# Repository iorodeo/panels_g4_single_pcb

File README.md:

## panels_g4_single_pcb

Prototype designs for a single PCB G4 panels variant.

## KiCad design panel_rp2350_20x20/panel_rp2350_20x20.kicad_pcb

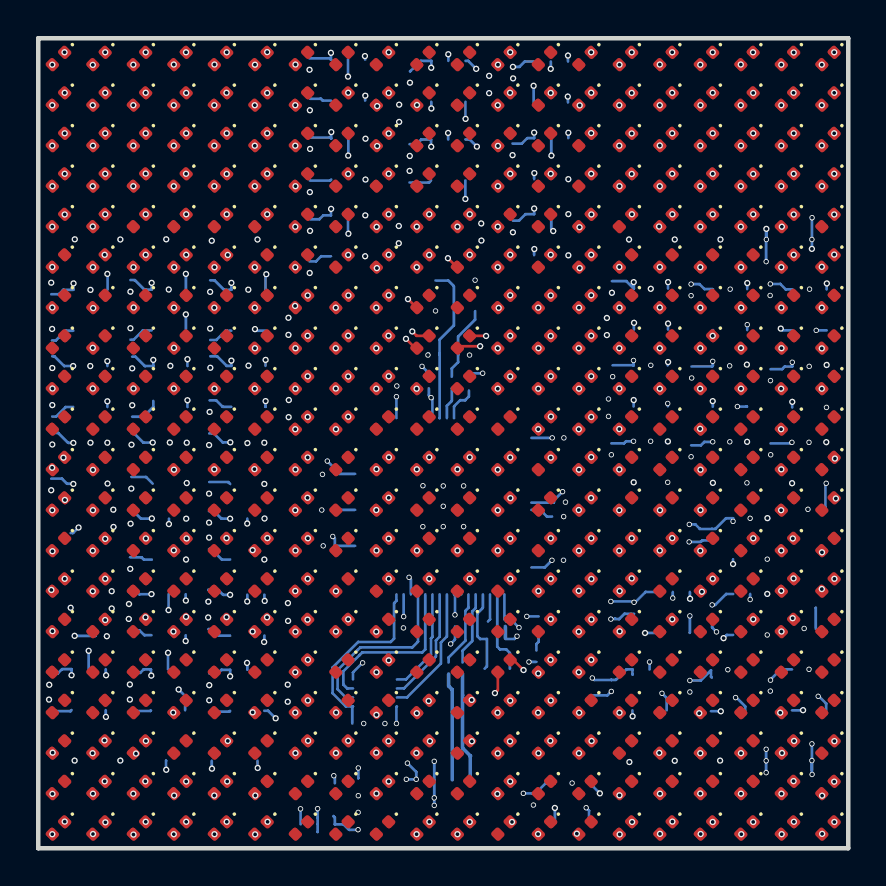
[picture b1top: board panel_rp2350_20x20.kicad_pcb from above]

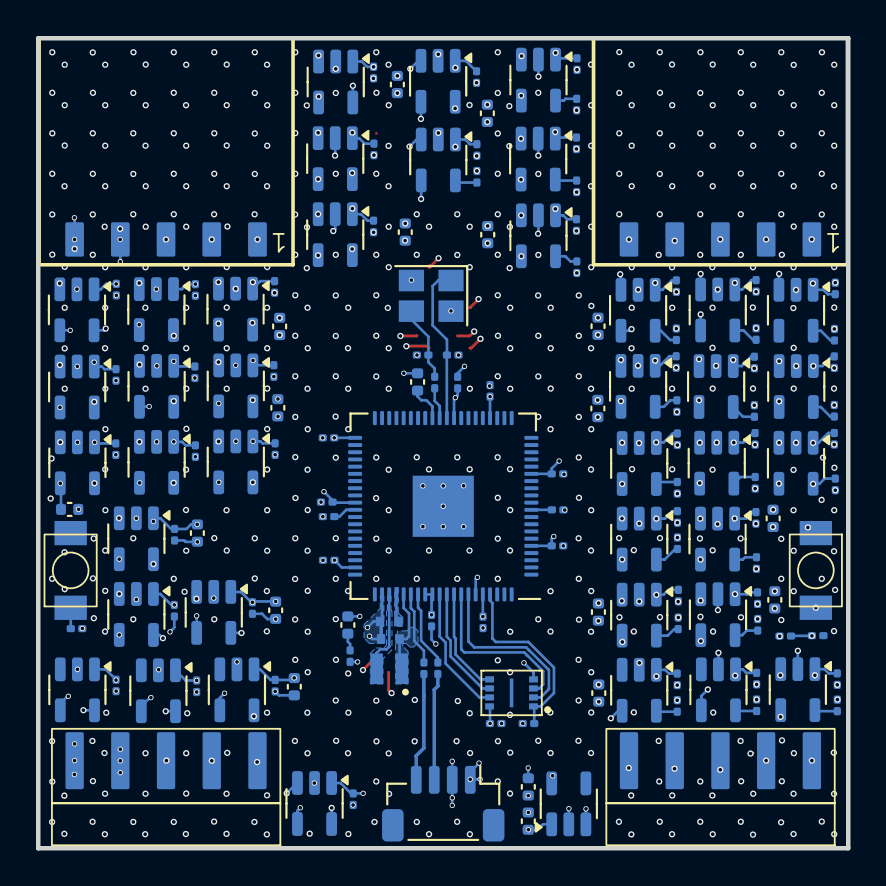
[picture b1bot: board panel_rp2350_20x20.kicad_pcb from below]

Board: 6 copper layers, 45.0 x 45.0 mm, 556 parts (156 on the bottom side), 131 nets.

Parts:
C1, C2: 15pF; C_0201_0603Metric
C3, C6, C9, C10, C11, C12, C13, C14, C15, C16, C17, C18, C19, C20, C21, C22, C23, C24, C25, C26, C27, C28, C29, C30, C31, C32, C33, C34, C35, C36, C37, C38, C39, C40, C41, C42, C43, C44, C45, C46, C47, C48, C49, C50, C51, C52, C53, C54, C55, C56, C57, C58: 100nF; C_0201_0603Metric
C4, C5: 4.7uF; C_0402_1005Metric_small_pads
C7, C8: 4.7uF; C_0402_1005Metric
C59, C60, C61, C62, C63, C64, C65, C66, C67, C68, C69, C70, C71, C72, C73, C74, C75, C76: 10uF; C_0402_1005Metric
D1: LED_T0; LED_0402_1005Metric
D2, D3, D4, D5, D6, D7, D8, D9, D10, D11, D12, D13, D14, D15, D16, D17, D18, D19, D20, D21, D22, D23, D24, D25, D26, D27, D28, D29, D30, D31, D32, D33, D34, D35, D36, D37, D38, D39, D40, D41, D42, D43, D44, D45, D46, D47, D48, D49, D50, D51, D52, D53, D54, D55, D56, D57, D58, D59, D60, D61, D62, D63, D64, D65, D66, D67, D68, D69, D70, D71, D72, D73, D74, D75, D76, D77, D78, D79, D80, D81, D82, D83, D84, D85, D86, D87, D88, D89, D90, D91, D92, D93, D94, D95, D96, D97, D98, D99, D100, D101, D102, D103, D104, D105, D106, D107, D108, D109, D110, D111, D112, D113, D114, D115, D116, D117, D118, D119, D120, D121, D122, D123, D124, D125, D126, D127, D128, D129, D130, D131, D132, D133, D134, D135, D136, D137, D138, D139, D140, D141, D142, D143, D144, D145, D146, D147, D148, D149, D150, D151, D152, D153, D154, D155, D156, D157, D158, D159, D160, D161, D162, D163, D164, D165, D166, D167, D168, D169, D170, D171, D172, D173, D174, D175, D176, D177, D178, D179, D180, D181, D182, D183, D184, D185, D186, D187, D188, D189, D190, D191, D192, D193, D194, D195, D196, D197, D198, D199, D200, D201, D202, D203, D204, D205, D206, D207, D208, D209, D210, D211, D212, D213, D214, D215, D216, D217, D218, D219, D220, D221, D222, D223, D224, D225, D226, D227, D228, D229, D230, D231, D232, D233, D234, D235, D236, D237, D238, D239, D240, D241, D242, D243, D244, D245, D246, D247, D248, D249, D250, D251, D252, D253, D254, D255, D256, D257, D258, D259, D260, D261, D262, D263, D264, D265, D266, D267, D268, D269, D270, D271, D272, D273, D274, D275, D276, D277, D278, D279, D280, D281, D282, D283, D284, D285, D286, D287, D288, D289, D290, D291, D292, D293, D294, D295, D296, D297, D298, D299, D300, D301, D302, D303, D304, D305, D306, D307, D308, D309, D310, D311, D312, D313, D314, D315, D316, D317, D318, D319, D320, D321, D322, D323, D324, D325, D326, D327, D328, D329, D330, D331, D332, D333, D334, D335, D336, D337, D338, D339, D340, D341, D342, D343, D344, D345, D346, D347, D348, D349, D350, D351, D352, D353, D354, D355, D356, D357, D358, D359, D360, D361, D362, D363, D364, D365, D366, D367, D368, D369, D370, D371, D372, D373, D374, D375, D376, D377, D378, D379, D380, D381, D382, D383, D384, D385, D386, D387, D388, D389, D390, D391, D392, D393, D394, D395, D396, D397, D398, D399, D400: LED; LED_0402_1005Metric
J1: Conn_01x04; JST_SH_BM04B-SRSS-TB_1x04-1MP_P1.00mm_Vertical
J2, J3: Conn_01x05; PinHeader_1x5_M20-8890545R
J4, J5: Conn_01x05; ConnRcpt_1x5_SMH-105-02-X-S
L1: 3.3uH; L_pol_2016
R1, R4: 10k; R_0201_0603Metric
R2, R3, R5: 1k; R_0201_0603Metric
R6: 33; R_0201_0603Metric
R7, R8: 27; R_0201_0603Metric
R9, R10, R11, R12, R13, R14, R15, R16, R17, R18, R19, R20, R21, R22, R23, R24, R25, R26, R27, R28: 270; R_0201_0603Metric
SW1, SW2: SW_Push; TS-1088-AR02016
U1: APS6404L-3SQR; flashmem_PSON50P300X200X60-9N
U2: RP2354B_80QFN; RP2350-QFN-80-1EP_10x10_P0.4mm_EP3.4x3.4mm_ThermalVias
U3, U4, U5, U6, U7, U8, U9, U10, U11, U12, U13, U14, U15, U16, U17, U18, U19, U20, U21, U22, U23, U24, U25, U26, U27, U28, U29, U30, U31, U32, U33, U34, U35, U36, U37, U38, U39, U40, U41, U42: UCC27517; SOT-23-5
U43: AP2112K-3.3; SOT-23-5
Y1: ABM8-272-T3; Crystal_SMD_3225-4Pin_3.2x2.5mm

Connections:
+1V1: C5.1, C6.1, C8.1, C9.1, L1.1, U2.10 (DVDD), U2.32 (DVDD), U2.51 (DVDD), U2.65 (VREG_FB)
+3V3: C3.1, C4.1, C10.1, C11.1, C12.1, C13.1, C14.1, C15.1, C16.1, C17.1, C18.1, C68.1, R1.1, R4.1, R6.1, U1.8 (VCC), U2.5 (IOVDD), U2.15 (IOVDD), U2.24 (IOVDD), U2.29 (IOVDD), U2.41 (IOVDD), U2.50 (IOVDD), U2.59 (ADC_AVDD), U2.60 (IOVDD), U2.64 (VREG_VIN), U2.68 (USB_OTP_VDD), U2.69 (QSPI_IOVDD), U2.76 (IOVDD), U43.5 (VOUT)
+5V: C19.1, C20.1, C21.1, C22.1, C23.1, C24.1, C25.1, C26.1, C27.1, C28.1, C29.1, C30.1, C31.1, C32.1, C33.1, C34.1, C35.1, C36.1, C37.1, C38.1, C39.1, C40.1, C41.1, C42.1, C43.1, C44.1, C45.1, C46.1, C47.1, C48.1, C49.1, C50.1, C51.1, C52.1, C53.1, C54.1, C55.1, C56.1, C57.1, C58.1, C59.1, C60.1, C61.1, C62.1, C63.1, C64.1, C65.1, C66.1, C67.1, C69.1, C70.1, C71.1, C72.1, C73.1, C74.1, C75.1, C76.1, J1.2, J2.5, J4.5, U3.1 (VDD), U4.1 (VDD), U5.1 (VDD), U6.1 (VDD), U7.1 (VDD), U8.1 (VDD), U9.1 (VDD), U10.1 (VDD), U11.1 (VDD), U12.1 (VDD), U13.1 (VDD), U14.1 (VDD), U15.1 (VDD), U16.1 (VDD), U17.1 (VDD), U18.1 (VDD), U19.1 (VDD), U20.1 (VDD), U21.1 (VDD), U22.1 (VDD), U23.1 (VDD), U24.1 (VDD), U25.1 (VDD), U26.1 (VDD), U27.1 (VDD), U28.1 (VDD), U29.1 (VDD), U30.1 (VDD), U31.1 (VDD), U32.1 (VDD), U33.1 (VDD), U34.1 (VDD), U35.1 (VDD), U36.1 (VDD), U37.1 (VDD), U38.1 (VDD), U39.1 (VDD), U40.1 (VDD), U41.1 (VDD), U42.1 (VDD), U43.1 (VIN), U43.3 (EN)
/drivers/COL_00: R9.1, U3.5 (OUT)
/drivers/COL_01: R10.1, U4.5 (OUT)
/drivers/COL_02: R11.1, U5.5 (OUT)
/drivers/COL_03: R12.1, U6.5 (OUT)
/drivers/COL_04: R13.1, U7.5 (OUT)
/drivers/COL_05: R14.1, U8.5 (OUT)
/drivers/COL_06: R15.1, U9.5 (OUT)
/drivers/COL_07: R16.1, U10.5 (OUT)
/drivers/COL_08: R17.1, U11.5 (OUT)
/drivers/COL_09: R18.1, U12.5 (OUT)
/drivers/COL_10: R19.1, U13.5 (OUT)
/drivers/COL_11: R20.1, U14.5 (OUT)
/drivers/COL_12: R21.1, U15.5 (OUT)
/drivers/COL_13: R22.1, U16.5 (OUT)
/drivers/COL_14: R23.1, U17.5 (OUT)
/drivers/COL_15: R24.1, U18.5 (OUT)
/drivers/COL_16: R25.1, U19.5 (OUT)
/drivers/COL_17: R26.1, U20.5 (OUT)
/drivers/COL_18: R27.1, U21.5 (OUT)
/drivers/COL_19: R28.1, U22.5 (OUT)
/drivers/COL_MCU_00: U2.78 (GPIO1), U3.3 (IN+)
/drivers/COL_MCU_01: U2.79 (GPIO2), U4.3 (IN+)
/drivers/COL_MCU_02: U2.80 (GPIO3), U5.3 (IN+)
/drivers/COL_MCU_03: U2.1 (GPIO4), U6.3 (IN+)
/drivers/COL_MCU_04: U2.2 (GPIO5), U7.3 (IN+)
/drivers/COL_MCU_05: U2.3 (GPIO6), U8.3 (IN+)
/drivers/COL_MCU_06: U2.4 (GPIO7), U9.3 (IN+)
/drivers/COL_MCU_07: U2.6 (GPIO8), U10.3 (IN+)
/drivers/COL_MCU_08: U2.7 (GPIO9), U11.3 (IN+)
/drivers/COL_MCU_09: U2.8 (GPIO10), U12.3 (IN+)
/drivers/COL_MCU_10: U2.9 (GPIO11), U13.3 (IN+)
/drivers/COL_MCU_11: U2.11 (GPIO12), U14.3 (IN+)
/drivers/COL_MCU_12: U2.12 (GPIO13), U15.3 (IN+)
/drivers/COL_MCU_13: U2.13 (GPIO14), U16.3 (IN+)
/drivers/COL_MCU_14: U2.14 (GPIO15), U17.3 (IN+)
/drivers/COL_MCU_15: U2.16 (GPIO16), U18.3 (IN+)
/drivers/COL_MCU_16: U2.17 (GPIO17), U19.3 (IN+)
/drivers/COL_MCU_17: U2.18 (GPIO18), U20.3 (IN+)
/drivers/COL_MCU_18: U2.19 (GPIO19), U21.3 (IN+)
/drivers/COL_MCU_19: U2.20 (GPIO20), U22.3 (IN+)
/drivers/ROW_00: D1.1 (K), D21.1 (K), D41.1 (K), D61.1 (K), D81.1 (K), D101.1 (K), D121.1 (K), D141.1 (K), D161.1 (K), D181.1 (K), D201.1 (K), D221.1 (K), D241.1 (K), D261.1 (K), D281.1 (K), D301.1 (K), D321.1 (K), D341.1 (K), D361.1 (K), D381.1 (K), U23.5 (OUT)
/drivers/ROW_01: D2.1 (K), D22.1 (K), D42.1 (K), D62.1 (K), D82.1 (K), D102.1 (K), D122.1 (K), D142.1 (K), D162.1 (K), D182.1 (K), D202.1 (K), D222.1 (K), D242.1 (K), D262.1 (K), D282.1 (K), D302.1 (K), D322.1 (K), D342.1 (K), D362.1 (K), D382.1 (K), U24.5 (OUT)
/drivers/ROW_02: D3.1 (K), D23.1 (K), D43.1 (K), D63.1 (K), D83.1 (K), D103.1 (K), D123.1 (K), D143.1 (K), D163.1 (K), D183.1 (K), D203.1 (K), D223.1 (K), D243.1 (K), D263.1 (K), D283.1 (K), D303.1 (K), D323.1 (K), D343.1 (K), D363.1 (K), D383.1 (K), U25.5 (OUT)
/drivers/ROW_03: D4.1 (K), D24.1 (K), D44.1 (K), D64.1 (K), D84.1 (K), D104.1 (K), D124.1 (K), D144.1 (K), D164.1 (K), D184.1 (K), D204.1 (K), D224.1 (K), D244.1 (K), D264.1 (K), D284.1 (K), D304.1 (K), D324.1 (K), D344.1 (K), D364.1 (K), D384.1 (K), U26.5 (OUT)
/drivers/ROW_04: D5.1 (K), D25.1 (K), D45.1 (K), D65.1 (K), D85.1 (K), D105.1 (K), D125.1 (K), D145.1 (K), D165.1 (K), D185.1 (K), D205.1 (K), D225.1 (K), D245.1 (K), D265.1 (K), D285.1 (K), D305.1 (K), D325.1 (K), D345.1 (K), D365.1 (K), D385.1 (K), U27.5 (OUT)
/drivers/ROW_05: D6.1 (K), D26.1 (K), D46.1 (K), D66.1 (K), D86.1 (K), D106.1 (K), D126.1 (K), D146.1 (K), D166.1 (K), D186.1 (K), D206.1 (K), D226.1 (K), D246.1 (K), D266.1 (K), D286.1 (K), D306.1 (K), D326.1 (K), D346.1 (K), D366.1 (K), D386.1 (K), U28.5 (OUT)
/drivers/ROW_06: D7.1 (K), D27.1 (K), D47.1 (K), D67.1 (K), D87.1 (K), D107.1 (K), D127.1 (K), D147.1 (K), D167.1 (K), D187.1 (K), D207.1 (K), D227.1 (K), D247.1 (K), D267.1 (K), D287.1 (K), D307.1 (K), D327.1 (K), D347.1 (K), D367.1 (K), D387.1 (K), U29.5 (OUT)
/drivers/ROW_07: D8.1 (K), D28.1 (K), D48.1 (K), D68.1 (K), D88.1 (K), D108.1 (K), D128.1 (K), D148.1 (K), D168.1 (K), D188.1 (K), D208.1 (K), D228.1 (K), D248.1 (K), D268.1 (K), D288.1 (K), D308.1 (K), D328.1 (K), D348.1 (K), D368.1 (K), D388.1 (K), U30.5 (OUT)
/drivers/ROW_08: D9.1 (K), D29.1 (K), D49.1 (K), D69.1 (K), D89.1 (K), D109.1 (K), D129.1 (K), D149.1 (K), D169.1 (K), D189.1 (K), D209.1 (K), D229.1 (K), D249.1 (K), D269.1 (K), D289.1 (K), D309.1 (K), D329.1 (K), D349.1 (K), D369.1 (K), D389.1 (K), U31.5 (OUT)
/drivers/ROW_09: D10.1 (K), D30.1 (K), D50.1 (K), D70.1 (K), D90.1 (K), D110.1 (K), D130.1 (K), D150.1 (K), D170.1 (K), D190.1 (K), D210.1 (K), D230.1 (K), D250.1 (K), D270.1 (K), D290.1 (K), D310.1 (K), D330.1 (K), D350.1 (K), D370.1 (K), D390.1 (K), U32.5 (OUT)
/drivers/ROW_10: D11.1 (K), D31.1 (K), D51.1 (K), D71.1 (K), D91.1 (K), D111.1 (K), D131.1 (K), D151.1 (K), D171.1 (K), D191.1 (K), D211.1 (K), D231.1 (K), D251.1 (K), D271.1 (K), D291.1 (K), D311.1 (K), D331.1 (K), D351.1 (K), D371.1 (K), D391.1 (K), U33.5 (OUT)
/drivers/ROW_11: D12.1 (K), D32.1 (K), D52.1 (K), D72.1 (K), D92.1 (K), D112.1 (K), D132.1 (K), D152.1 (K), D172.1 (K), D192.1 (K), D212.1 (K), D232.1 (K), D252.1 (K), D272.1 (K), D292.1 (K), D312.1 (K), D332.1 (K), D352.1 (K), D372.1 (K), D392.1 (K), U34.5 (OUT)
/drivers/ROW_12: D13.1 (K), D33.1 (K), D53.1 (K), D73.1 (K), D93.1 (K), D113.1 (K), D133.1 (K), D153.1 (K), D173.1 (K), D193.1 (K), D213.1 (K), D233.1 (K), D253.1 (K), D273.1 (K), D293.1 (K), D313.1 (K), D333.1 (K), D353.1 (K), D373.1 (K), D393.1 (K), U35.5 (OUT)
/drivers/ROW_13: D14.1 (K), D34.1 (K), D54.1 (K), D74.1 (K), D94.1 (K), D114.1 (K), D134.1 (K), D154.1 (K), D174.1 (K), D194.1 (K), D214.1 (K), D234.1 (K), D254.1 (K), D274.1 (K), D294.1 (K), D314.1 (K), D334.1 (K), D354.1 (K), D374.1 (K), D394.1 (K), U36.5 (OUT)
/drivers/ROW_14: D15.1 (K), D35.1 (K), D55.1 (K), D75.1 (K), D95.1 (K), D115.1 (K), D135.1 (K), D155.1 (K), D175.1 (K), D195.1 (K), D215.1 (K), D235.1 (K), D255.1 (K), D275.1 (K), D295.1 (K), D315.1 (K), D335.1 (K), D355.1 (K), D375.1 (K), D395.1 (K), U37.5 (OUT)
/drivers/ROW_15: D16.1 (K), D36.1 (K), D56.1 (K), D76.1 (K), D96.1 (K), D116.1 (K), D136.1 (K), D156.1 (K), D176.1 (K), D196.1 (K), D216.1 (K), D236.1 (K), D256.1 (K), D276.1 (K), D296.1 (K), D316.1 (K), D336.1 (K), D356.1 (K), D376.1 (K), D396.1 (K), U38.5 (OUT)
/drivers/ROW_16: D17.1 (K), D37.1 (K), D57.1 (K), D77.1 (K), D97.1 (K), D117.1 (K), D137.1 (K), D157.1 (K), D177.1 (K), D197.1 (K), D217.1 (K), D237.1 (K), D257.1 (K), D277.1 (K), D297.1 (K), D317.1 (K), D337.1 (K), D357.1 (K), D377.1 (K), D397.1 (K), U39.5 (OUT)
/drivers/ROW_17: D18.1 (K), D38.1 (K), D58.1 (K), D78.1 (K), D98.1 (K), D118.1 (K), D138.1 (K), D158.1 (K), D178.1 (K), D198.1 (K), D218.1 (K), D238.1 (K), D258.1 (K), D278.1 (K), D298.1 (K), D318.1 (K), D338.1 (K), D358.1 (K), D378.1 (K), D398.1 (K), U40.5 (OUT)
/drivers/ROW_18: D19.1 (K), D39.1 (K), D59.1 (K), D79.1 (K), D99.1 (K), D119.1 (K), D139.1 (K), D159.1 (K), D179.1 (K), D199.1 (K), D219.1 (K), D239.1 (K), D259.1 (K), D279.1 (K), D299.1 (K), D319.1 (K), D339.1 (K), D359.1 (K), D379.1 (K), D399.1 (K), U41.5 (OUT)
/drivers/ROW_19: D20.1 (K), D40.1 (K), D60.1 (K), D80.1 (K), D100.1 (K), D120.1 (K), D140.1 (K), D160.1 (K), D180.1 (K), D200.1 (K), D220.1 (K), D240.1 (K), D260.1 (K), D280.1 (K), D300.1 (K), D320.1 (K), D340.1 (K), D360.1 (K), D380.1 (K), D400.1 (K), U42.5 (OUT)
/drivers/ROW_MCU_00: U2.21 (GPIO21), U23.3 (IN+)
/drivers/ROW_MCU_01: U2.22 (GPIO22), U24.3 (IN+)
/drivers/ROW_MCU_02: U2.23 (GPIO23), U25.3 (IN+)
/drivers/ROW_MCU_03: U2.25 (GPIO24), U26.3 (IN+)
/drivers/ROW_MCU_04: U2.26 (GPIO25), U27.3 (IN+)
/drivers/ROW_MCU_05: U2.27 (GPIO26), U28.3 (IN+)
/drivers/ROW_MCU_06: U2.28 (GPIO27), U29.3 (IN+)
/drivers/ROW_MCU_07: U2.36 (GPIO28), U30.3 (IN+)
/drivers/ROW_MCU_08: U2.37 (GPIO29), U31.3 (IN+)
/drivers/ROW_MCU_09: U2.38 (GPIO30), U32.3 (IN+)
/drivers/ROW_MCU_10: U2.39 (GPIO31), U33.3 (IN+)
/drivers/ROW_MCU_11: U2.45 (GPIO36), U34.3 (IN+)
/drivers/ROW_MCU_12: U2.46 (GPIO37), U35.3 (IN+)
/drivers/ROW_MCU_13: U2.47 (GPIO38), U36.3 (IN+)
/drivers/ROW_MCU_14: U2.48 (GPIO39), U37.3 (IN+)
/drivers/ROW_MCU_15: U2.49 (GPIO40_ADC0), U38.3 (IN+)
/drivers/ROW_MCU_16: U2.52 (GPIO41_ADC1), U39.3 (IN+)
/drivers/ROW_MCU_17: U2.53 (GPIO42_ADC2), U40.3 (IN+)
/drivers/ROW_MCU_18: U2.54 (GPIO43_ADC3), U41.3 (IN+)
/drivers/ROW_MCU_19: U2.55 (GPIO44_ADC4), U42.3 (IN+)
/panel_header/CS0: J3.5, U2.42 (GPIO33)
/panel_header/CS1: J3.4, J5.5
/panel_header/CS2: J3.3, J5.4
/panel_header/CS4: J3.2, J5.3
/panel_header/EINT: J3.1, J5.1
/panel_header/MISO: J2.1, J4.1, U2.44 (GPIO35)
/panel_header/MOSI: J2.2, J4.2, U2.40 (GPIO32)
/panel_header/SCK: J2.3, J4.3, U2.43 (GPIO34)
/panel_mcu/D+: J1.3, R7.1
/panel_mcu/D-: J1.4, R8.1
/panel_mcu/QSPI_SCLK: U1.6 (CLK), U2.71 (QSPI_SCLK)
/panel_mcu/QSPI_SD0: U1.5 (IO0), U2.72 (QSPI_SD0)
/panel_mcu/QSPI_SD1: U1.2 (IO1), U2.74 (QSPI_SD1)
/panel_mcu/QSPI_SD2: U1.3 (IO2), U2.73 (QSPI_SD2)
/panel_mcu/QSPI_SD3: U1.7 (IO3), U2.70 (QSPI_SD3)
/panel_mcu/QSPI_SS: R3.1, R4.2, U2.75 (QSPI_SS)
/panel_mcu/RUN: SW2.2, U2.35 (RUN)
/panel_mcu/VREG_AVDD: C7.1, R6.2, U2.61 (VREG_AVDD)
/panel_mcu/VREG_LX: L1.2, U2.63 (VREG_LX)
/panel_mcu/XIN: C1.1, U2.30 (XIN), Y1.1
/panel_mcu/XIP_CS1n: R1.2, U1.1 (~CS), U2.77 (GPIO0)
/panel_mcu/XOUT: R5.1, U2.31 (XOUT)
/panel_mcu/~USB_BOOT: R3.2, SW1.2
GND: C1.2, C2.2, C3.2, C4.2, C5.2, C6.2, C7.2, C8.2, C9.2, C10.2, C11.2, C12.2, C13.2, C14.2, C15.2, C16.2, C17.2, C18.2, C19.2, C20.2, C21.2, C22.2, C23.2, C24.2, C25.2, C26.2, C27.2, C28.2, C29.2, C30.2, C31.2, C32.2, C33.2, C34.2, C35.2, C36.2, C37.2, C38.2, C39.2, C40.2, C41.2, C42.2, C43.2, C44.2, C45.2, C46.2, C47.2, C48.2, C49.2, C50.2, C51.2, C52.2, C53.2, C54.2, C55.2, C56.2, C57.2, C58.2, C59.2, C60.2, C61.2, C62.2, C63.2, C64.2, C65.2, C66.2, C67.2, C68.2, C69.2, C70.2, C71.2, C72.2, C73.2, C74.2, C75.2, C76.2, J1.1, J2.4, J4.4, R2.2, SW1.1, U1.4 (GND), U2.62 (VREG_PGND), U2.81 (GND), U3.2 (GND), U3.4 (IN-), U4.2 (GND), U4.4 (IN-), U5.2 (GND), U5.4 (IN-), U6.2 (GND), U6.4 (IN-), U7.2 (GND), U7.4 (IN-), U8.2 (GND), U8.4 (IN-), U9.2 (GND), U9.4 (IN-), U10.2 (GND), U10.4 (IN-), U11.2 (GND), U11.4 (IN-), U12.2 (GND), U12.4 (IN-), U13.2 (GND), U13.4 (IN-), U14.2 (GND), U14.4 (IN-), U15.2 (GND), U15.4 (IN-), U16.2 (GND), U16.4 (IN-), U17.2 (GND), U17.4 (IN-), U18.2 (GND), U18.4 (IN-), U19.2 (GND), U19.4 (IN-), U20.2 (GND), U20.4 (IN-), U21.2 (GND), U21.4 (IN-), U22.2 (GND), U22.4 (IN-), U23.2 (GND), U23.4 (IN-), U24.2 (GND), U24.4 (IN-), U25.2 (GND), U25.4 (IN-), U26.2 (GND), U26.4 (IN-), U27.2 (GND), U27.4 (IN-), U28.2 (GND), U28.4 (IN-), U29.2 (GND), U29.4 (IN-), U30.2 (GND), U30.4 (IN-), U31.2 (GND), U31.4 (IN-), U32.2 (GND), U32.4 (IN-), U33.2 (GND), U33.4 (IN-), U34.2 (GND), U34.4 (IN-), U35.2 (GND), U35.4 (IN-), U36.2 (GND), U36.4 (IN-), U37.2 (GND), U37.4 (IN-), U38.2 (GND), U38.4 (IN-), U39.2 (GND), U39.4 (IN-), U40.2 (GND), U40.4 (IN-), U41.2 (GND), U41.4 (IN-), U42.2 (GND), U42.4 (IN-), U43.2 (GND), Y1.2, Y1.4
unnamed: C2.1, R5.2, Y1.3
unnamed: D1.2 (A), D2.2 (A), D3.2 (A), D4.2 (A), D5.2 (A), D6.2 (A), D7.2 (A), D8.2 (A), D9.2 (A), D10.2 (A), D11.2 (A), D12.2 (A), D13.2 (A), D14.2 (A), D15.2 (A), D16.2 (A), D17.2 (A), D18.2 (A), D19.2 (A), D20.2 (A), R9.2
unnamed: D21.2 (A), D22.2 (A), D23.2 (A), D24.2 (A), D25.2 (A), D26.2 (A), D27.2 (A), D28.2 (A), D29.2 (A), D30.2 (A), D31.2 (A), D32.2 (A), D33.2 (A), D34.2 (A), D35.2 (A), D36.2 (A), D37.2 (A), D38.2 (A), D39.2 (A), D40.2 (A), R10.2
unnamed: D41.2 (A), D42.2 (A), D43.2 (A), D44.2 (A), D45.2 (A), D46.2 (A), D47.2 (A), D48.2 (A), D49.2 (A), D50.2 (A), D51.2 (A), D52.2 (A), D53.2 (A), D54.2 (A), D55.2 (A), D56.2 (A), D57.2 (A), D58.2 (A), D59.2 (A), D60.2 (A), R11.2
unnamed: D61.2 (A), D62.2 (A), D63.2 (A), D64.2 (A), D65.2 (A), D66.2 (A), D67.2 (A), D68.2 (A), D69.2 (A), D70.2 (A), D71.2 (A), D72.2 (A), D73.2 (A), D74.2 (A), D75.2 (A), D76.2 (A), D77.2 (A), D78.2 (A), D79.2 (A), D80.2 (A), R12.2
unnamed: D81.2 (A), D82.2 (A), D83.2 (A), D84.2 (A), D85.2 (A), D86.2 (A), D87.2 (A), D88.2 (A), D89.2 (A), D90.2 (A), D91.2 (A), D92.2 (A), D93.2 (A), D94.2 (A), D95.2 (A), D96.2 (A), D97.2 (A), D98.2 (A), D99.2 (A), D100.2 (A), R13.2
unnamed: D101.2 (A), D102.2 (A), D103.2 (A), D104.2 (A), D105.2 (A), D106.2 (A), D107.2 (A), D108.2 (A), D109.2 (A), D110.2 (A), D111.2 (A), D112.2 (A), D113.2 (A), D114.2 (A), D115.2 (A), D116.2 (A), D117.2 (A), D118.2 (A), D119.2 (A), D120.2 (A), R14.2
unnamed: D121.2 (A), D122.2 (A), D123.2 (A), D124.2 (A), D125.2 (A), D126.2 (A), D127.2 (A), D128.2 (A), D129.2 (A), D130.2 (A), D131.2 (A), D132.2 (A), D133.2 (A), D134.2 (A), D135.2 (A), D136.2 (A), D137.2 (A), D138.2 (A), D139.2 (A), D140.2 (A), R15.2
unnamed: D141.2 (A), D142.2 (A), D143.2 (A), D144.2 (A), D145.2 (A), D146.2 (A), D147.2 (A), D148.2 (A), D149.2 (A), D150.2 (A), D151.2 (A), D152.2 (A), D153.2 (A), D154.2 (A), D155.2 (A), D156.2 (A), D157.2 (A), D158.2 (A), D159.2 (A), D160.2 (A), R16.2
unnamed: D161.2 (A), D162.2 (A), D163.2 (A), D164.2 (A), D165.2 (A), D166.2 (A), D167.2 (A), D168.2 (A), D169.2 (A), D170.2 (A), D171.2 (A), D172.2 (A), D173.2 (A), D174.2 (A), D175.2 (A), D176.2 (A), D177.2 (A), D178.2 (A), D179.2 (A), D180.2 (A), R17.2
unnamed: D181.2 (A), D182.2 (A), D183.2 (A), D184.2 (A), D185.2 (A), D186.2 (A), D187.2 (A), D188.2 (A), D189.2 (A), D190.2 (A), D191.2 (A), D192.2 (A), D193.2 (A), D194.2 (A), D195.2 (A), D196.2 (A), D197.2 (A), D198.2 (A), D199.2 (A), D200.2 (A), R18.2
unnamed: D201.2 (A), D202.2 (A), D203.2 (A), D204.2 (A), D205.2 (A), D206.2 (A), D207.2 (A), D208.2 (A), D209.2 (A), D210.2 (A), D211.2 (A), D212.2 (A), D213.2 (A), D214.2 (A), D215.2 (A), D216.2 (A), D217.2 (A), D218.2 (A), D219.2 (A), D220.2 (A), R19.2
unnamed: D221.2 (A), D222.2 (A), D223.2 (A), D224.2 (A), D225.2 (A), D226.2 (A), D227.2 (A), D228.2 (A), D229.2 (A), D230.2 (A), D231.2 (A), D232.2 (A), D233.2 (A), D234.2 (A), D235.2 (A), D236.2 (A), D237.2 (A), D238.2 (A), D239.2 (A), D240.2 (A), R20.2
unnamed: D241.2 (A), D242.2 (A), D243.2 (A), D244.2 (A), D245.2 (A), D246.2 (A), D247.2 (A), D248.2 (A), D249.2 (A), D250.2 (A), D251.2 (A), D252.2 (A), D253.2 (A), D254.2 (A), D255.2 (A), D256.2 (A), D257.2 (A), D258.2 (A), D259.2 (A), D260.2 (A), R21.2
unnamed: D261.2 (A), D262.2 (A), D263.2 (A), D264.2 (A), D265.2 (A), D266.2 (A), D267.2 (A), D268.2 (A), D269.2 (A), D270.2 (A), D271.2 (A), D272.2 (A), D273.2 (A), D274.2 (A), D275.2 (A), D276.2 (A), D277.2 (A), D278.2 (A), D279.2 (A), D280.2 (A), R22.2
unnamed: D281.2 (A), D282.2 (A), D283.2 (A), D284.2 (A), D285.2 (A), D286.2 (A), D287.2 (A), D288.2 (A), D289.2 (A), D290.2 (A), D291.2 (A), D292.2 (A), D293.2 (A), D294.2 (A), D295.2 (A), D296.2 (A), D297.2 (A), D298.2 (A), D299.2 (A), D300.2 (A), R23.2
unnamed: D301.2 (A), D302.2 (A), D303.2 (A), D304.2 (A), D305.2 (A), D306.2 (A), D307.2 (A), D308.2 (A), D309.2 (A), D310.2 (A), D311.2 (A), D312.2 (A), D313.2 (A), D314.2 (A), D315.2 (A), D316.2 (A), D317.2 (A), D318.2 (A), D319.2 (A), D320.2 (A), R24.2
unnamed: D321.2 (A), D322.2 (A), D323.2 (A), D324.2 (A), D325.2 (A), D326.2 (A), D327.2 (A), D328.2 (A), D329.2 (A), D330.2 (A), D331.2 (A), D332.2 (A), D333.2 (A), D334.2 (A), D335.2 (A), D336.2 (A), D337.2 (A), D338.2 (A), D339.2 (A), D340.2 (A), R25.2
unnamed: D341.2 (A), D342.2 (A), D343.2 (A), D344.2 (A), D345.2 (A), D346.2 (A), D347.2 (A), D348.2 (A), D349.2 (A), D350.2 (A), D351.2 (A), D352.2 (A), D353.2 (A), D354.2 (A), D355.2 (A), D356.2 (A), D357.2 (A), D358.2 (A), D359.2 (A), D360.2 (A), R26.2
unnamed: D361.2 (A), D362.2 (A), D363.2 (A), D364.2 (A), D365.2 (A), D366.2 (A), D367.2 (A), D368.2 (A), D369.2 (A), D370.2 (A), D371.2 (A), D372.2 (A), D373.2 (A), D374.2 (A), D375.2 (A), D376.2 (A), D377.2 (A), D378.2 (A), D379.2 (A), D380.2 (A), R27.2
unnamed: D381.2 (A), D382.2 (A), D383.2 (A), D384.2 (A), D385.2 (A), D386.2 (A), D387.2 (A), D388.2 (A), D389.2 (A), D390.2 (A), D391.2 (A), D392.2 (A), D393.2 (A), D394.2 (A), D395.2 (A), D396.2 (A), D397.2 (A), D398.2 (A), D399.2 (A), D400.2 (A), R28.2
unnamed: R2.1, SW2.1
unnamed: R8.2, U2.66 (USB_DM)
unnamed: R7.2, U2.67 (USB_DP)

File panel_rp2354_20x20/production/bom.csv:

Designator,Footprint,Quantity,Value,LCSC Part #
"C1, C2",0201,2,15pF,C541259
"C10, C11, C12, C13, C14, C15, C16, C17, C18, C19, C20, C21, C22, C23, C24, C25, C26, C27, C28, C29, C3, C30, C31, C32, C33, C34, C35, C36, C37, C38, C39, C40, C41, C42, C43, C44, C45, C46, C47, C48, C49, C50, C51, C52, C53, C54, C55, C56, C57, C58, C6, C9",0201,52,100nF,C76939
"C4, C5, C7, C8",0402,4,4.7uF,C368809
"C59, C60, C61, C62, C63, C64, C65, C66, C67, C68, C69, C70, C71, C72, C73, C74, C75, C76",0402,18,10uF,C315248
"D1, D10, D100, D11, D12, D13, D14, D15, D16, D161, D162, D163, D164, D165, D166, D167, D168, D169, D17, D170, D171, D172, D173, D174, D175, D176, D177, D178, D179, D18, D180, D19, D2, D20, D241, D242, D243, D244, D245, D246, D247, D248, D249, D250, D251, D252, D253, D254, D255, D256, D257, D258, D259, D260, D3, D321, D322, D323, D324, D325, D326, D327, D328, D329, D330, D331, D332, D333, D334, D335, D336, D337, D338, D339, D340, D4, D5, D6, D7, D8, D81, D82, D83, D84, D85, D86, D87, D88, D89, D9, D90, D91, D92, D93, D94, D95, D96, D97, D98, D99",0402,100,LED_T0,C273601
"D101, D102, D103, D104, D105, D106, D107, D108, D109, D110, D111, D112, D113, D114, D115, D116, D117, D118, D119, D120, D181, D182, D183, D184, D185, D186, D187, D188, D189, D190, D191, D192, D193, D194, D195, D196, D197, D198, D199, D200, D21, D22, D23, D24, D25, D26, D261, D262, D263, D264, D265, D266, D267, D268, D269, D27, D270, D271, D272, D273, D274, D275, D276, D277, D278, D279, D28, D280, D29, D30, D31, D32, D33, D34, D341, D342, D343, D344, D345, D346, D347, D348, D349, D35, D350, D351, D352, D353, D354, D355, D356, D357, D358, D359, D36, D360, D37, D38, D39, D40",0402,100,LED_T1,C131223
"D121, D122, D123, D124, D125, D126, D127, D128, D129, D130, D131, D132, D133, D134, D135, D136, D137, D138, D139, D140, D201, D202, D203, D204, D205, D206, D207, D208, D209, D210, D211, D212, D213, D214, D215, D216, D217, D218, D219, D220, D281, D282, D283, D284, D285, D286, D287, D288, D289, D290, D291, D292, D293, D294, D295, D296, D297, D298, D299, D300, D361, D362, D363, D364, D365, D366, D367, D368, D369, D370, D371, D372, D373, D374, D375, D376, D377, D378, D379, D380, D41, D42, D43, D44, D45, D46, D47, D48, D49, D50, D51, D52, D53, D54, D55, D56, D57, D58, D59, D60",0402,100,LED_T2,C131223
"D141, D142, D143, D144, D145, D146, D147, D148, D149, D150, D151, D152, D153, D154, D155, D156, D157, D158, D159, D160, D221, D222, D223, D224, D225, D226, D227, D228, D229, D230, D231, D232, D233, D234, D235, D236, D237, D238, D239, D240, D301, D302, D303, D304, D305, D306, D307, D308, D309, D310, D311, D312, D313, D314, D315, D316, D317, D318, D319, D320, D381, D382, D383, D384, D385, D386, D387, D388, D389, D390, D391, D392, D393, D394, D395, D396, D397, D398, D399, D400, D61, D62, D63, D64, D65, D66, D67, D68, D69, D70, D71, D72, D73, D74, D75, D76, D77, D78, D79, D80",0402,100,LED_T3,C273601
J1,JST_SH_BM04B-SRSS-TB_1x04-1MP_P1.00mm_Vertical,1,Conn_01x04,C160390
"J2, J3",PinHeader_1x5_M20-8890545R,2,Conn_01x05,C6585819
"J4, J5",ConnRcpt_1x5_SMH-105-02-X-S,2,Conn_01x05,C21116902 
L1,L_pol_2016,1,3.3uH,C42411119
"R1, R4",0201,2,10k,C473048
"R10, R11, R14, R15, R18, R19, R22, R23, R26, R27",0201,10,165,C320715
"R12, R13, R16, R17, R20, R21, R24, R25, R28, R9",0201,10,270,C320799
"R2, R3, R5",0201,3,1k,C270365
R6,0201,1,33,C295794
"R7, R8",0201,2,27,C473051
"SW1, SW2",TS-1088-AR02016,2,SW_Push,C720477
U1,flashmem_PSON50P300X200X60-9N,1,APS6404L-3SQR,C3040877
"U10, U11, U12, U13, U14, U15, U16, U17, U18, U19, U20, U21, U22, U23, U24, U25, U26, U27, U28, U29, U3, U30, U31, U32, U33, U34, U35, U36, U37, U38, U39, U4, U40, U41, U42, U5, U6, U7, U8, U9",SOT-23-5,40,UCC27517,C99395
U2,RP2350-QFN-80-1EP_10x10_P0.4mm_EP3.4x3.4mm_ThermalVias,1,RP2354B_80QFN,C39843328
U43,SOT-23-5,1,AP2112K-3.3,C51118
Y1,Crystal_SMD_3225-4Pin_3.2x2.5mm,1,ABM8-272-T3,C20625731

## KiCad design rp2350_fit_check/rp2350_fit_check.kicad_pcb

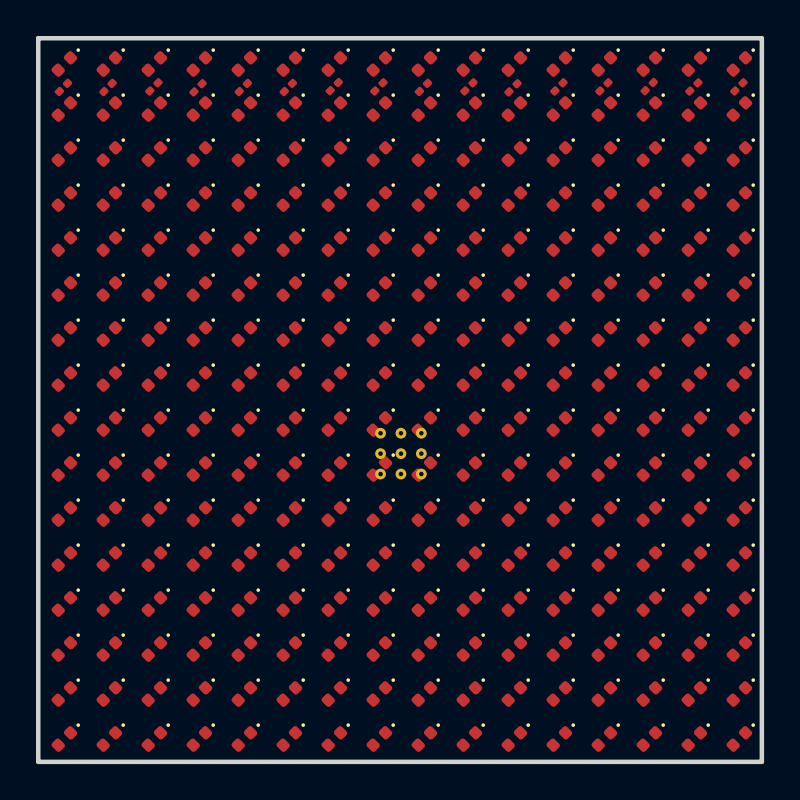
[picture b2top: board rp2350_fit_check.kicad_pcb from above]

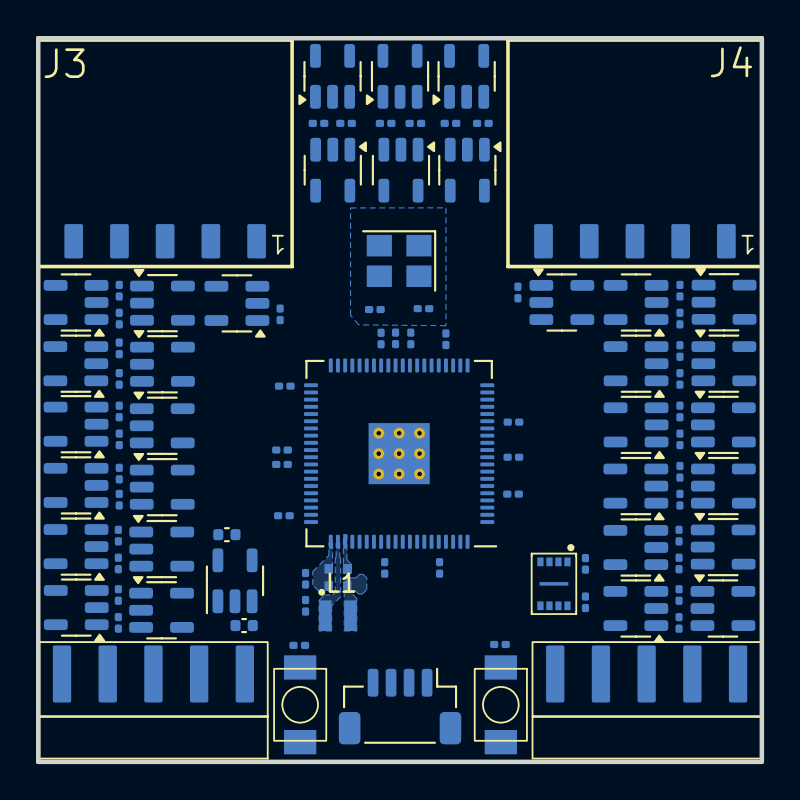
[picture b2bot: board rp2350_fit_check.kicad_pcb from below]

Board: 6 copper layers, 40.2 x 40.2 mm, 269 parts (13 on the bottom side), 42 nets, no tracks yet.

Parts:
C1, C2: 10uF; C_0402_1005Metric
C6, C7: 4.7u; C_0402_1005Metric_small_pads
D1, D2, D3, D4, D5, D6, D7, D8, D9, D10, D11, D12, D13, D14, D15, D16, D17, D18, D19, D20, D21, D22, D23, D24, D25, D26, D27, D28, D29, D30, D31, D32, D33, D34, D35, D36, D37, D38, D39, D40, D41, D42, D43, D44, D45, D46, D47, D48, D49, D50, D51, D52, D53, D54, D55, D56, D57, D58, D59, D60, D61, D62, D63, D64, D65, D66, D67, D68, D69, D70, D71, D72, D73, D74, D75, D76, D77, D78, D79, D80, D81, D82, D83, D84, D85, D86, D87, D88, D89, D90, D91, D92, D93, D94, D95, D96, D97, D98, D99, D100, D101, D102, D103, D104, D105, D106, D107, D108, D109, D110, D111, D112, D113, D114, D115, D116, D117, D118, D119, D120, D121, D122, D123, D124, D125, D126, D127, D128, D129, D130, D131, D132, D133, D134, D135, D136, D137, D138, D139, D140, D141, D142, D143, D144, D145, D146, D147, D148, D149, D150, D151, D152, D153, D154, D155, D156, D157, D158, D159, D160, D161, D162, D163, D164, D165, D166, D167, D168, D169, D170, D171, D172, D173, D174, D175, D176, D177, D178, D179, D180, D181, D182, D183, D184, D185, D186, D187, D188, D189, D190, D191, D192, D193, D194, D195, D196, D197, D198, D199, D200, D201, D202, D203, D204, D205, D206, D207, D208, D209, D210, D211, D212, D213, D214, D215, D216, D217, D218, D219, D220, D221, D222, D223, D224, D225, D226, D227, D228, D229, D230, D231, D232, D233, D234, D235, D236, D237, D238, D239, D240, D241, D242, D243, D244, D245, D246, D247, D248, D249, D250, D251, D252, D253, D254, D255, D256: LED; LED_0402_1005Metric
J1, J2: Conn_01x05; PinHeader_1x5_M20-8890545R
J3, J4: Conn_01x05; ConnRcpt_1x5_SMH-105-02-X-S
L1: 4.7u; L_pol_2016
SW1, SW2: SW_Push; TS-1088-AR02016
U1: AP2112K-3.3; SOT-23-5
Y1: ABM8-272-T3; Crystal_SMD_3225-4Pin_3.2x2.5mm

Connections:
+3.3V: C2.1, SW1.1, U1.5 (VOUT)
+5V: C1.1, J1.5, J3.5, U1.1 (VIN), U1.3 (EN)
/level_shifter/CP_5V_00: D1.1 (K), D2.1 (K), D3.1 (K), D4.1 (K), D5.1 (K), D6.1 (K), D7.1 (K), D8.1 (K), D9.1 (K), D10.1 (K), D11.1 (K), D12.1 (K), D13.1 (K), D14.1 (K), D15.1 (K), D16.1 (K)
/level_shifter/CP_5V_01: D1.2 (A), D17.1 (K), D18.1 (K), D19.1 (K), D20.1 (K), D21.1 (K), D22.1 (K), D23.1 (K), D24.1 (K), D25.1 (K), D26.1 (K), D27.1 (K), D28.1 (K), D29.1 (K), D30.1 (K), D31.1 (K), D32.1 (K), D34.2 (A), D50.2 (A), D66.2 (A), D82.2 (A), D98.2 (A), D114.2 (A), D130.2 (A), D146.2 (A), D162.2 (A), D178.2 (A), D194.2 (A), D210.2 (A), D226.2 (A), D242.2 (A)
/level_shifter/CP_5V_02: D33.1 (K), D34.1 (K), D35.1 (K), D36.1 (K), D37.1 (K), D38.1 (K), D39.1 (K), D40.1 (K), D41.1 (K), D42.1 (K), D43.1 (K), D44.1 (K), D45.1 (K), D46.1 (K), D47.1 (K), D48.1 (K)
/level_shifter/CP_5V_03: D49.1 (K), D50.1 (K), D51.1 (K), D52.1 (K), D53.1 (K), D54.1 (K), D55.1 (K), D56.1 (K), D57.1 (K), D58.1 (K), D59.1 (K), D60.1 (K), D61.1 (K), D62.1 (K), D63.1 (K), D64.1 (K)
/level_shifter/CP_5V_04: D65.1 (K), D66.1 (K), D67.1 (K), D68.1 (K), D69.1 (K), D70.1 (K), D71.1 (K), D72.1 (K), D73.1 (K), D74.1 (K), D75.1 (K), D76.1 (K), D77.1 (K), D78.1 (K), D79.1 (K), D80.1 (K)
/level_shifter/CP_5V_05: D81.1 (K), D82.1 (K), D83.1 (K), D84.1 (K), D85.1 (K), D86.1 (K), D87.1 (K), D88.1 (K), D89.1 (K), D90.1 (K), D91.1 (K), D92.1 (K), D93.1 (K), D94.1 (K), D95.1 (K), D96.1 (K)
/level_shifter/CP_5V_06: D97.1 (K), D98.1 (K), D99.1 (K), D100.1 (K), D101.1 (K), D102.1 (K), D103.1 (K), D104.1 (K), D105.1 (K), D106.1 (K), D107.1 (K), D108.1 (K), D109.1 (K), D110.1 (K), D111.1 (K), D112.1 (K)
/level_shifter/CP_5V_07: D113.1 (K), D114.1 (K), D115.1 (K), D116.1 (K), D117.1 (K), D118.1 (K), D119.1 (K), D120.1 (K), D121.1 (K), D122.1 (K), D123.1 (K), D124.1 (K), D125.1 (K), D126.1 (K), D127.1 (K), D128.1 (K)
/level_shifter/CP_5V_08: D129.1 (K), D130.1 (K), D131.1 (K), D132.1 (K), D133.1 (K), D134.1 (K), D135.1 (K), D136.1 (K), D137.1 (K), D138.1 (K), D139.1 (K), D140.1 (K), D141.1 (K), D142.1 (K), D143.1 (K), D144.1 (K)
/level_shifter/CP_5V_09: D145.1 (K), D146.1 (K), D147.1 (K), D148.1 (K), D149.1 (K), D150.1 (K), D151.1 (K), D152.1 (K), D153.1 (K), D154.1 (K), D155.1 (K), D156.1 (K), D157.1 (K), D158.1 (K), D159.1 (K), D160.1 (K)
/level_shifter/CP_5V_10: D161.1 (K), D162.1 (K), D163.1 (K), D164.1 (K), D165.1 (K), D166.1 (K), D167.1 (K), D168.1 (K), D169.1 (K), D170.1 (K), D171.1 (K), D172.1 (K), D173.1 (K), D174.1 (K), D175.1 (K), D176.1 (K)
/level_shifter/CP_5V_11: D177.1 (K), D178.1 (K), D179.1 (K), D180.1 (K), D181.1 (K), D182.1 (K), D183.1 (K), D184.1 (K), D185.1 (K), D186.1 (K), D187.1 (K), D188.1 (K), D189.1 (K), D190.1 (K), D191.1 (K), D192.1 (K)
/level_shifter/CP_5V_12: D193.1 (K), D194.1 (K), D195.1 (K), D196.1 (K), D197.1 (K), D198.1 (K), D199.1 (K), D200.1 (K), D201.1 (K), D202.1 (K), D203.1 (K), D204.1 (K), D205.1 (K), D206.1 (K), D207.1 (K), D208.1 (K)
/level_shifter/CP_5V_13: D209.1 (K), D210.1 (K), D211.1 (K), D212.1 (K), D213.1 (K), D214.1 (K), D215.1 (K), D216.1 (K), D217.1 (K), D218.1 (K), D219.1 (K), D220.1 (K), D221.1 (K), D222.1 (K), D223.1 (K), D224.1 (K)
/level_shifter/CP_5V_14: D225.1 (K), D226.1 (K), D227.1 (K), D228.1 (K), D229.1 (K), D230.1 (K), D231.1 (K), D232.1 (K), D233.1 (K), D234.1 (K), D235.1 (K), D236.1 (K), D237.1 (K), D238.1 (K), D239.1 (K), D240.1 (K)
/level_shifter/CP_5V_15: D241.1 (K), D242.1 (K), D243.1 (K), D244.1 (K), D245.1 (K), D246.1 (K), D247.1 (K), D248.1 (K), D249.1 (K), D250.1 (K), D251.1 (K), D252.1 (K), D253.1 (K), D254.1 (K), D255.1 (K), D256.1 (K)
/panel_header/CS1: J2.4, J4.5
/panel_header/CS2: J2.3, J4.4
/panel_header/CS4: J2.2, J4.3
/panel_header/CS5: J2.1, J4.2
/panel_header/MISO: J1.1, J3.1
/panel_header/MOSI: J1.2, J3.2
/panel_header/SCK: J1.3, J3.3
GND: C1.2, C2.2, C6.2, C7.2, J1.4, J3.4, SW1.2, SW2.2, U1.2 (GND), Y1.2, Y1.4
unnamed: D10.2 (A), D26.2 (A), D42.2 (A), D58.2 (A), D74.2 (A), D90.2 (A), D106.2 (A), D122.2 (A), D138.2 (A), D154.2 (A), D187.2 (A), D203.2 (A), D219.2 (A), D235.2 (A), D251.2 (A)
unnamed: D3.2 (A), D19.2 (A), D35.2 (A), D68.2 (A), D84.2 (A), D100.2 (A), D116.2 (A), D132.2 (A), D148.2 (A), D164.2 (A), D180.2 (A), D196.2 (A), D212.2 (A), D228.2 (A), D244.2 (A)
unnamed: D4.2 (A), D20.2 (A), D36.2 (A), D52.2 (A), D85.2 (A), D101.2 (A), D117.2 (A), D133.2 (A), D149.2 (A), D165.2 (A), D181.2 (A), D197.2 (A), D213.2 (A), D229.2 (A), D245.2 (A)
unnamed: D5.2 (A), D21.2 (A), D37.2 (A), D53.2 (A), D69.2 (A), D102.2 (A), D118.2 (A), D134.2 (A), D150.2 (A), D166.2 (A), D182.2 (A), D198.2 (A), D214.2 (A), D230.2 (A), D246.2 (A)
unnamed: D7.2 (A), D23.2 (A), D39.2 (A), D55.2 (A), D71.2 (A), D87.2 (A), D103.2 (A), D136.2 (A), D152.2 (A), D168.2 (A), D184.2 (A), D200.2 (A), D216.2 (A), D232.2 (A), D248.2 (A)
unnamed: D8.2 (A), D24.2 (A), D40.2 (A), D56.2 (A), D72.2 (A), D88.2 (A), D104.2 (A), D120.2 (A), D153.2 (A), D169.2 (A), D185.2 (A), D201.2 (A), D217.2 (A), D233.2 (A), D249.2 (A)
unnamed: D9.2 (A), D25.2 (A), D41.2 (A), D57.2 (A), D73.2 (A), D89.2 (A), D105.2 (A), D121.2 (A), D137.2 (A), D170.2 (A), D186.2 (A), D202.2 (A), D218.2 (A), D234.2 (A), D250.2 (A)
unnamed: D11.2 (A), D27.2 (A), D43.2 (A), D59.2 (A), D75.2 (A), D91.2 (A), D107.2 (A), D123.2 (A), D139.2 (A), D155.2 (A), D171.2 (A), D204.2 (A), D220.2 (A), D236.2 (A), D252.2 (A)
unnamed: D12.2 (A), D28.2 (A), D44.2 (A), D60.2 (A), D76.2 (A), D92.2 (A), D108.2 (A), D124.2 (A), D140.2 (A), D156.2 (A), D172.2 (A), D188.2 (A), D221.2 (A), D237.2 (A), D253.2 (A)
unnamed: D13.2 (A), D29.2 (A), D45.2 (A), D61.2 (A), D77.2 (A), D93.2 (A), D109.2 (A), D125.2 (A), D141.2 (A), D157.2 (A), D173.2 (A), D189.2 (A), D205.2 (A), D238.2 (A), D254.2 (A)
unnamed: D14.2 (A), D30.2 (A), D46.2 (A), D62.2 (A), D78.2 (A), D94.2 (A), D110.2 (A), D126.2 (A), D142.2 (A), D158.2 (A), D174.2 (A), D190.2 (A), D206.2 (A), D222.2 (A), D255.2 (A)
unnamed: D15.2 (A), D31.2 (A), D47.2 (A), D63.2 (A), D79.2 (A), D95.2 (A), D111.2 (A), D127.2 (A), D143.2 (A), D159.2 (A), D175.2 (A), D191.2 (A), D207.2 (A), D223.2 (A), D239.2 (A)
unnamed: D16.2 (A), D32.2 (A), D48.2 (A), D64.2 (A), D80.2 (A), D96.2 (A), D112.2 (A), D128.2 (A), D144.2 (A), D160.2 (A), D176.2 (A), D192.2 (A), D208.2 (A), D224.2 (A), D240.2 (A), D256.2 (A)
unnamed: D17.2 (A), D33.2 (A), D49.2 (A), D65.2 (A), D81.2 (A), D97.2 (A), D113.2 (A), D129.2 (A), D145.2 (A), D161.2 (A), D177.2 (A), D193.2 (A), D209.2 (A), D225.2 (A), D241.2 (A)
unnamed: D2.2 (A), D18.2 (A), D51.2 (A), D67.2 (A), D83.2 (A), D99.2 (A), D115.2 (A), D131.2 (A), D147.2 (A), D163.2 (A), D179.2 (A), D195.2 (A), D211.2 (A), D227.2 (A), D243.2 (A)
unnamed: D6.2 (A), D22.2 (A), D38.2 (A), D54.2 (A), D70.2 (A), D86.2 (A), D119.2 (A), D135.2 (A), D151.2 (A), D167.2 (A), D183.2 (A), D199.2 (A), D215.2 (A), D231.2 (A), D247.2 (A)
